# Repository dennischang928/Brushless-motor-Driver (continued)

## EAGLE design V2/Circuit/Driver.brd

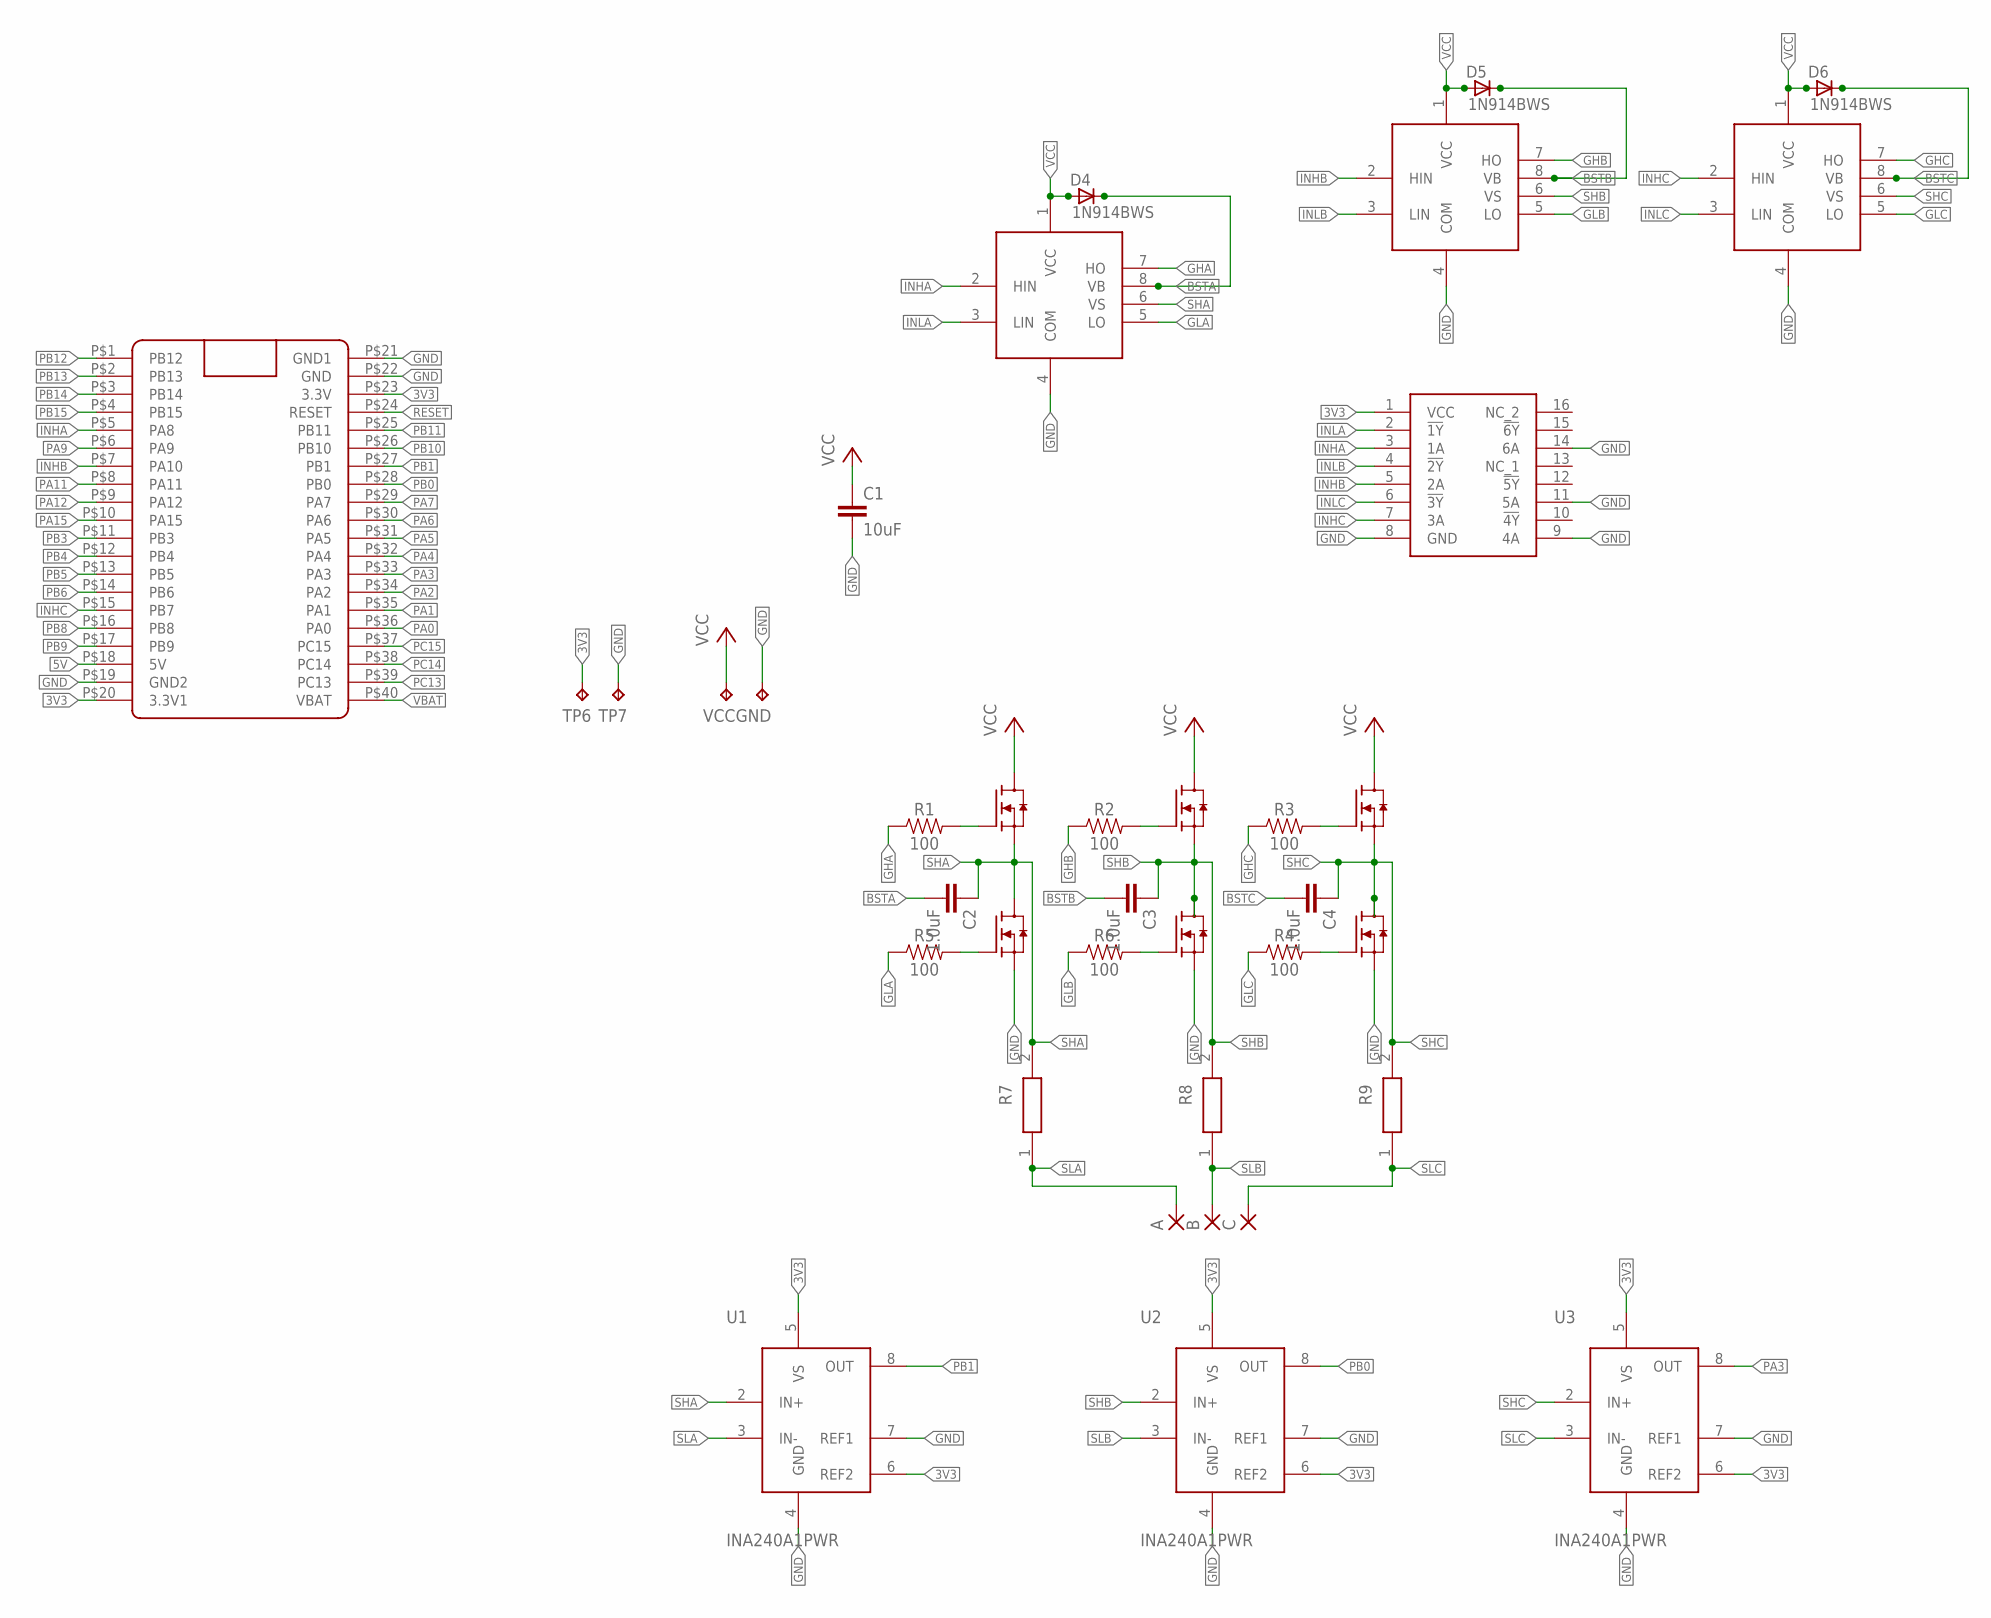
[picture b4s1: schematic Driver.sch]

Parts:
A: SMD5; SMD2,54-5,08
B: SMD5; SMD2,54-5,08
C: SMD5; SMD2,54-5,08
C1: 10uF; 0603
C2, C3, C4: 1.0uF; 0603
D4, D5, D6: 1N914BWS; SOD323F
GND: TPPAD1-13Y; P1-13Y
H-A: IRLR7843; TO252
H-B: IRLR7843; TO252
H-C: IRLR7843; TO252
IC2: CD74HC4049PWR; SOP65P640X120-16N
L-A: IRLR7843; TO252
L-B: IRLR7843; TO252
L-C: IRLR7843; TO252
R1, R2, R3, R4, R5, R6: 100; 0603
R7, R8, R9: CR2512-FX-51R1ELF; RESC6331X75N
TP6, TP7: TPPAD1-13Y; P1-13Y
U1, U2, U3: INA240A1PWR; SOP65P640X120-8N
U4, U5, U6: SOIC127P610X320-8NSOIC8; SOIC127P599X175-8N
U$1: BLUE_PILL
VCC: TPPAD1-13Y; P1-13Y

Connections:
3V3: IC2.1 (VCC), TP6.TP, U1.5 (VS), U1.6 (REF2), U2.5 (VS), U2.6 (REF2), U3.5 (VS), U3.6 (REF2), U$1.P$20 (3.3V1), U$1.P$23 (3.3V)
5V: U$1.P$18 (5V)
BSTA: C2.2, D4.C, U4.8 (VB)
BSTB: C3.2, D5.C, U5.8 (VB)
BSTC: C4.2, D6.C, U6.8 (VB)
GHA: R1.1, U4.7 (HO)
GHB: R2.1, U5.7 (HO)
GHC: R3.1, U6.7 (HO)
GLA: R5.1, U4.5 (LO)
GLB: R6.1, U5.5 (LO)
GLC: R4.1, U6.5 (LO)
GND: C1.2, GND.TP, IC2.8 (GND), IC2.9 (4A), IC2.11 (5A), IC2.14 (6A), L-A.2 (S), L-B.2 (S), L-C.2 (S), TP7.TP, U1.4 (GND), U1.7 (REF1), U2.4 (GND), U2.7 (REF1), U3.4 (GND), U3.7 (REF1), U4.4 (COM), U5.4 (COM), U6.4 (COM), U$1.P$19 (GND2), U$1.P$21 (GND1), U$1.P$22 (GND)
INHA: IC2.3 (1A), U4.2 (HIN), U$1.P$5 (PA8)
INHB: IC2.5 (2A), U5.2 (HIN), U$1.P$7 (PA10)
INHC: IC2.7 (3A), U6.2 (HIN), U$1.P$15 (PB7)
INLA: IC2.2 (!1Y), U4.3 (LIN)
INLB: IC2.4 (!2Y), U5.3 (LIN)
INLC: IC2.6 (!3Y), U6.3 (LIN)
unnamed: H-A.1 (G), R1.2
unnamed: H-B.1 (G), R2.2
unnamed: H-C.1 (G), R3.2
unnamed: L-A.1 (G), R5.2
unnamed: L-B.1 (G), R6.2
unnamed: L-C.1 (G), R4.2
PA0: U$1.P$36 (PA0)
PA1: U$1.P$35 (PA1)
PA2: U$1.P$34 (PA2)
PA3: U3.8 (OUT), U$1.P$33 (PA3)
PA4: U$1.P$32 (PA4)
PA5: U$1.P$31 (PA5)
PA6: U$1.P$30 (PA6)
PA7: U$1.P$29 (PA7)
PA9: U$1.P$6 (PA9)
PA11: U$1.P$8 (PA11)
PA12: U$1.P$9 (PA12)
PA15: U$1.P$10 (PA15)
PB0: U2.8 (OUT), U$1.P$28 (PB0)
PB1: U1.8 (OUT), U$1.P$27 (PB1)
PB3: U$1.P$11 (PB3)
PB4: U$1.P$12 (PB4)
PB5: U$1.P$13 (PB5)
PB6: U$1.P$14 (PB6)
PB8: U$1.P$16 (PB8)
PB9: U$1.P$17 (PB9)
PB10: U$1.P$26 (PB10)
PB11: U$1.P$25 (PB11)
PB12: U$1.P$1 (PB12)
PB13: U$1.P$2 (PB13)
PB14: U$1.P$3 (PB14)
PB15: U$1.P$4 (PB15)
PC13: U$1.P$39 (PC13)
PC14: U$1.P$38 (PC14)
PC15: U$1.P$37 (PC15)
RESET: U$1.P$24 (RESET)
SHA: C2.1, H-A.2 (S), L-A.3 (D), R7.2, U1.2 (IN+), U4.6 (VS)
SHB: C3.1, H-B.2 (S), L-B.3 (D), R8.2, U2.2 (IN+), U5.6 (VS)
SHC: C4.1, H-C.2 (S), L-C.3 (D), R9.2, U3.2 (IN+), U6.6 (VS)
SLA: A.1, R7.1, U1.3 (IN-)
SLB: B.1, R8.1, U2.3 (IN-)
SLC: C.1, R9.1, U3.3 (IN-)
VBAT: U$1.P$40 (VBAT)
VCC: C1.1, D4.A, D5.A, D6.A, H-A.3 (D), H-B.3 (D), H-C.3 (D), U4.1 (VCC), U5.1 (VCC), U6.1 (VCC), VCC.TP

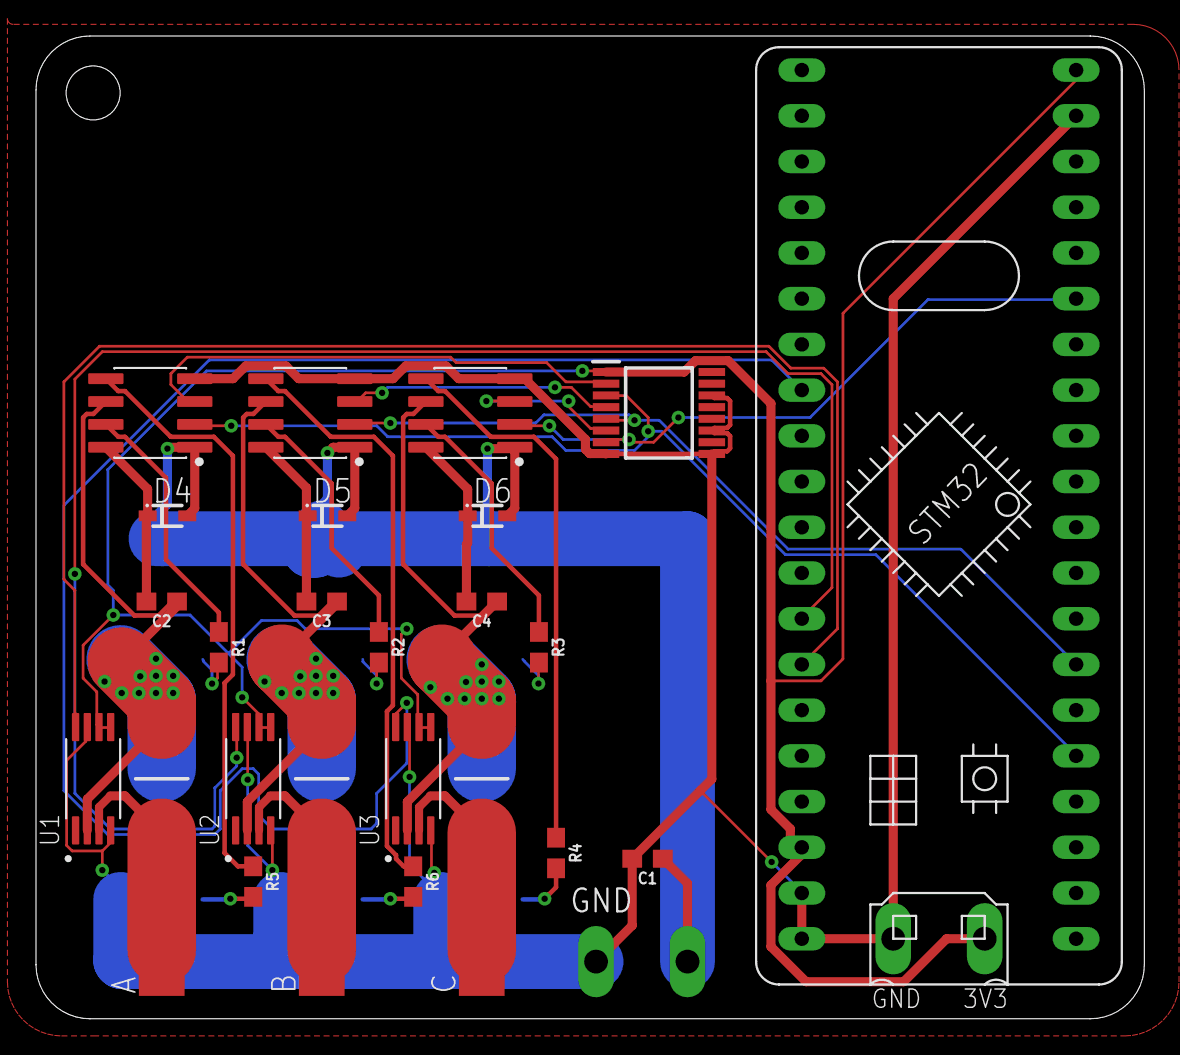
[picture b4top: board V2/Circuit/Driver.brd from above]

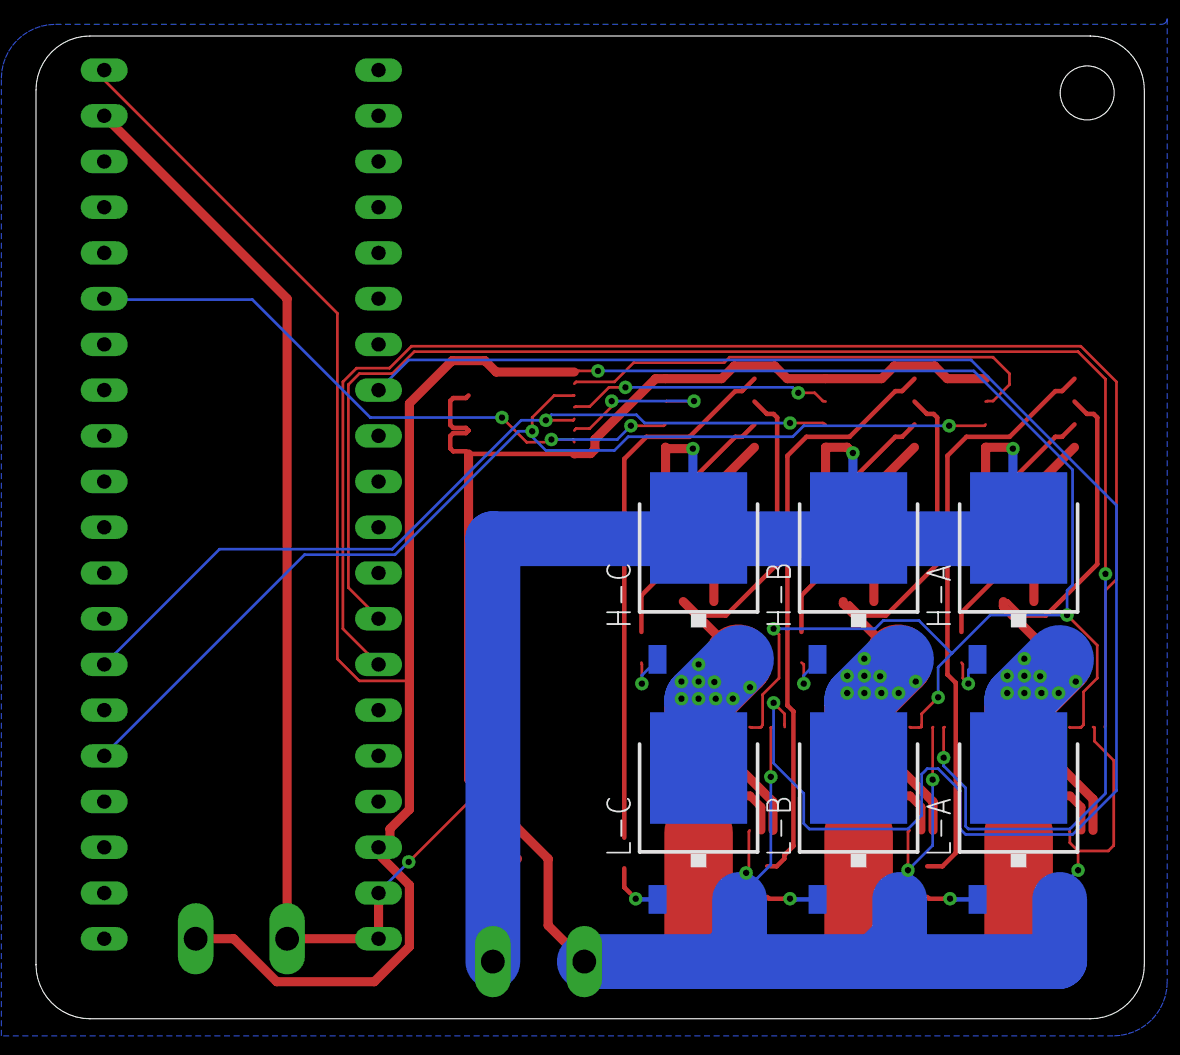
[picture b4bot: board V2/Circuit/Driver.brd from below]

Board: 2 copper layers, 61.6 x 54.6 mm, 37 parts (6 on the bottom side), 33 nets.

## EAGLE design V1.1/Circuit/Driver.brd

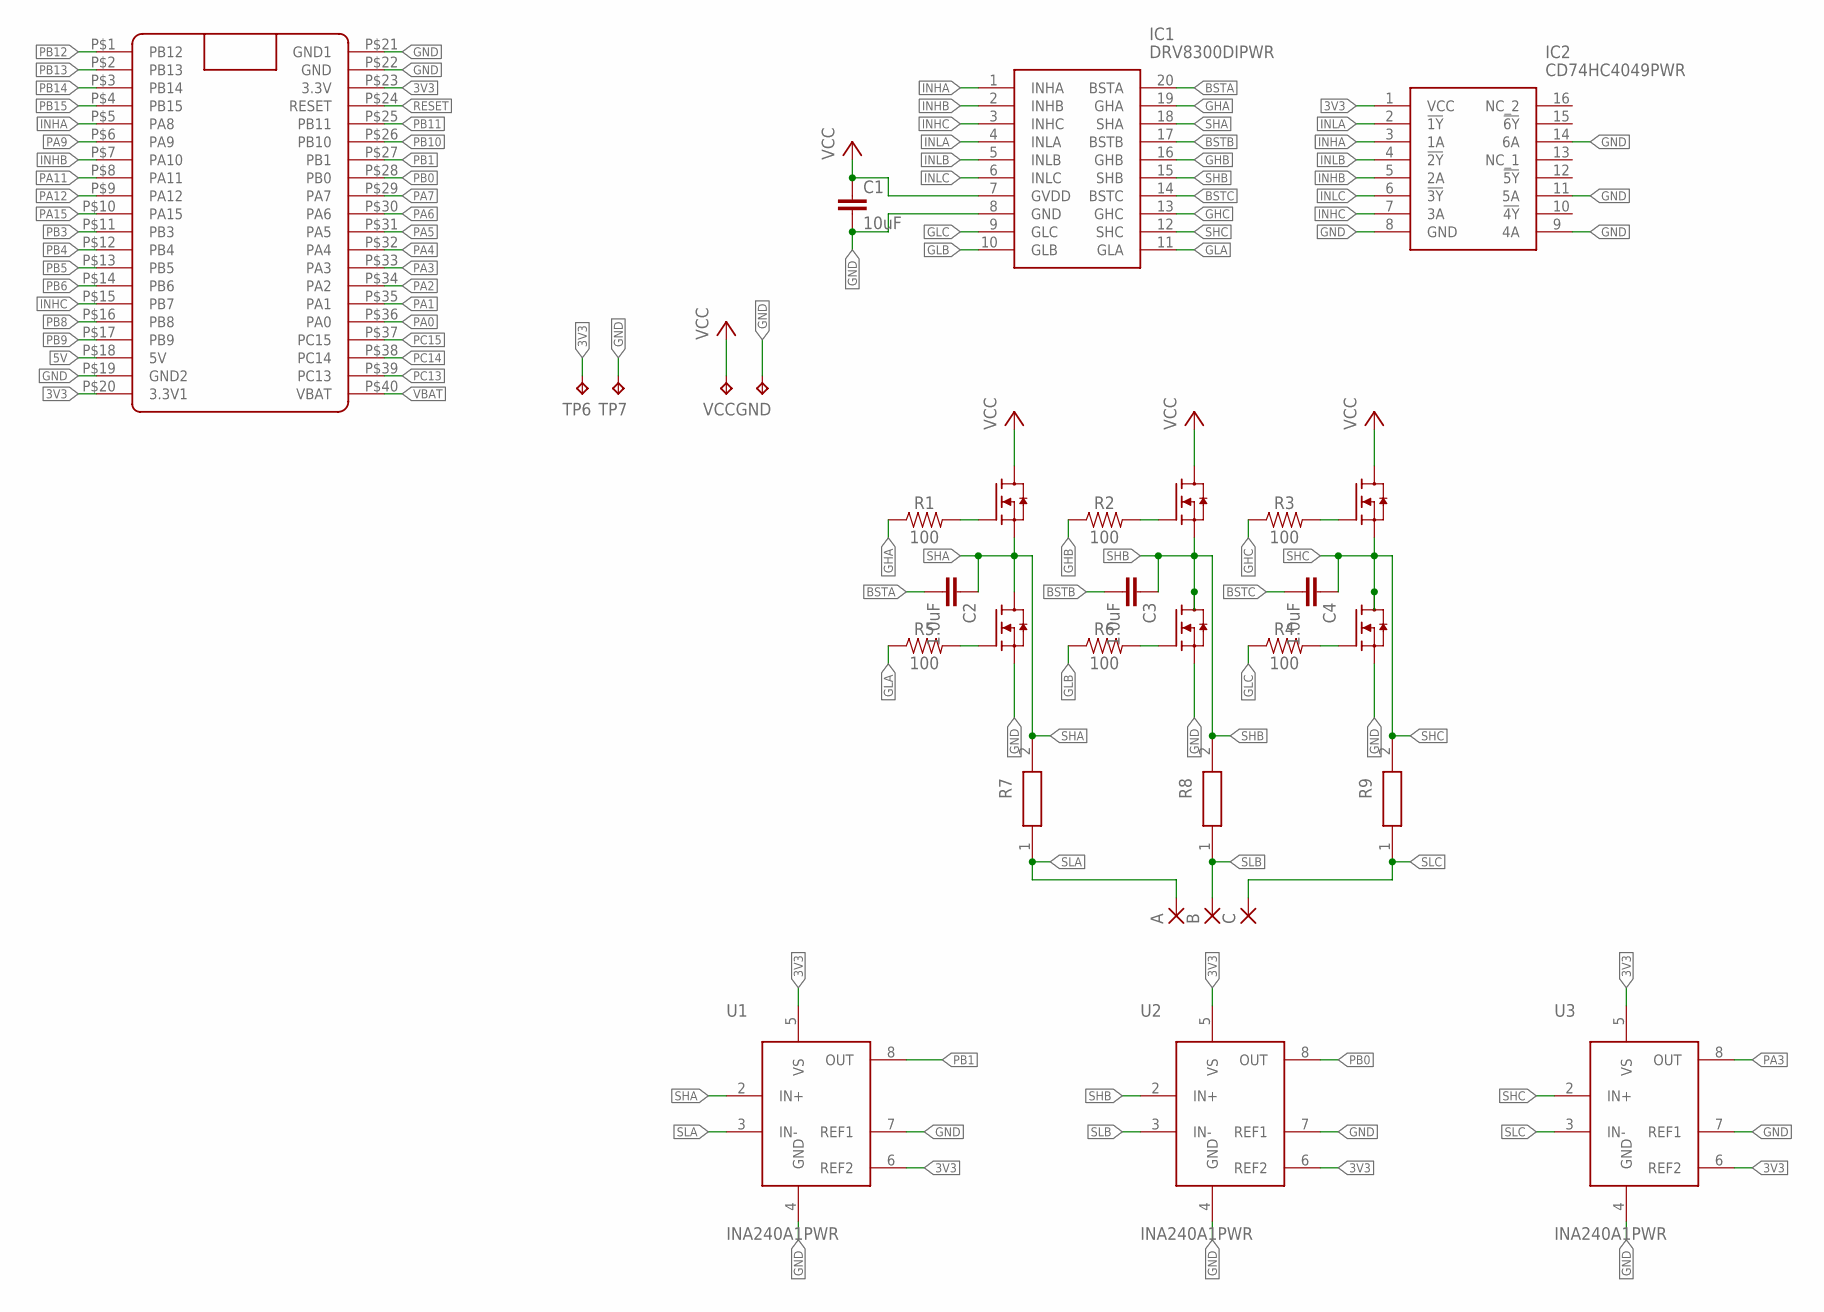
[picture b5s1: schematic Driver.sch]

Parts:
A: SMD5; SMD2,54-5,08
B: SMD5; SMD2,54-5,08
C: SMD5; SMD2,54-5,08
C1: 10uF; 0603
C2, C3, C4: 1.0uF; 0603
GND: TPPAD1-13Y; P1-13Y
IC1: DRV8300DIPWR; SOP65P640X120-20N
IC2: CD74HC4049PWR; SOP65P640X120-16N
R1, R2, R3, R4, R5, R6: 100; 0603
R7, R8, R9: CR2512-FX-51R1ELF; RESC6331X75N
TP6, TP7: TPPAD1-13Y; P1-13Y
U1, U2, U3: INA240A1PWR; SOP65P640X120-8N
U$1: BLUE_PILL
U$2, U$3, U$4, U$5, U$6, U$7: IRLR7843; TO252
VCC: TPPAD1-13Y; P1-13Y

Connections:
3V3: IC2.1 (VCC), TP6.TP, U1.5 (VS), U1.6 (REF2), U2.5 (VS), U2.6 (REF2), U3.5 (VS), U3.6 (REF2), U$1.P$20 (3.3V1), U$1.P$23 (3.3V)
5V: U$1.P$18 (5V)
BSTA: C2.2, IC1.20 (BSTA)
BSTB: C3.2, IC1.17 (BSTB)
BSTC: C4.2, IC1.14 (BSTC)
GHA: IC1.19 (GHA), R1.1
GHB: IC1.16 (GHB), R2.1
GHC: IC1.13 (GHC), R3.1
GLA: IC1.11 (GLA), R5.1
GLB: IC1.10 (GLB), R6.1
GLC: IC1.9 (GLC), R4.1
GND: C1.2, GND.TP, IC1.8 (GND), IC2.8 (GND), IC2.9 (4A), IC2.11 (5A), IC2.14 (6A), TP7.TP, U1.4 (GND), U1.7 (REF1), U2.4 (GND), U2.7 (REF1), U3.4 (GND), U3.7 (REF1), U$1.P$19 (GND2), U$1.P$21 (GND1), U$1.P$22 (GND), U$3.2 (S), U$5.2 (S), U$7.2 (S)
INHA: IC1.1 (INHA), IC2.3 (1A), U$1.P$5 (PA8)
INHB: IC1.2 (INHB), IC2.5 (2A), U$1.P$7 (PA10)
INHC: IC1.3 (INHC), IC2.7 (3A), U$1.P$15 (PB7)
INLA: IC1.4 (INLA), IC2.2 (!1Y)
INLB: IC1.5 (INLB), IC2.4 (!2Y)
INLC: IC1.6 (INLC), IC2.6 (!3Y)
unnamed: R1.2, U$2.1 (G)
unnamed: R2.2, U$4.1 (G)
unnamed: R3.2, U$6.1 (G)
unnamed: R5.2, U$3.1 (G)
unnamed: R6.2, U$5.1 (G)
unnamed: R4.2, U$7.1 (G)
PA0: U$1.P$36 (PA0)
PA1: U$1.P$35 (PA1)
PA2: U$1.P$34 (PA2)
PA3: U3.8 (OUT), U$1.P$33 (PA3)
PA4: U$1.P$32 (PA4)
PA5: U$1.P$31 (PA5)
PA6: U$1.P$30 (PA6)
PA7: U$1.P$29 (PA7)
PA9: U$1.P$6 (PA9)
PA11: U$1.P$8 (PA11)
PA12: U$1.P$9 (PA12)
PA15: U$1.P$10 (PA15)
PB0: U2.8 (OUT), U$1.P$28 (PB0)
PB1: U1.8 (OUT), U$1.P$27 (PB1)
PB3: U$1.P$11 (PB3)
PB4: U$1.P$12 (PB4)
PB5: U$1.P$13 (PB5)
PB6: U$1.P$14 (PB6)
PB8: U$1.P$16 (PB8)
PB9: U$1.P$17 (PB9)
PB10: U$1.P$26 (PB10)
PB11: U$1.P$25 (PB11)
PB12: U$1.P$1 (PB12)
PB13: U$1.P$2 (PB13)
PB14: U$1.P$3 (PB14)
PB15: U$1.P$4 (PB15)
PC13: U$1.P$39 (PC13)
PC14: U$1.P$38 (PC14)
PC15: U$1.P$37 (PC15)
RESET: U$1.P$24 (RESET)
SHA: C2.1, IC1.18 (SHA), R7.2, U1.2 (IN+), U$2.2 (S), U$3.3 (D)
SHB: C3.1, IC1.15 (SHB), R8.2, U2.2 (IN+), U$4.2 (S), U$5.3 (D)
SHC: C4.1, IC1.12 (SHC), R9.2, U3.2 (IN+), U$6.2 (S), U$7.3 (D)
SLA: A.1, R7.1, U1.3 (IN-)
SLB: B.1, R8.1, U2.3 (IN-)
SLC: C.1, R9.1, U3.3 (IN-)
VBAT: U$1.P$40 (VBAT)
VCC: C1.1, IC1.7 (GVDD), U$2.3 (D), U$4.3 (D), U$6.3 (D), VCC.TP

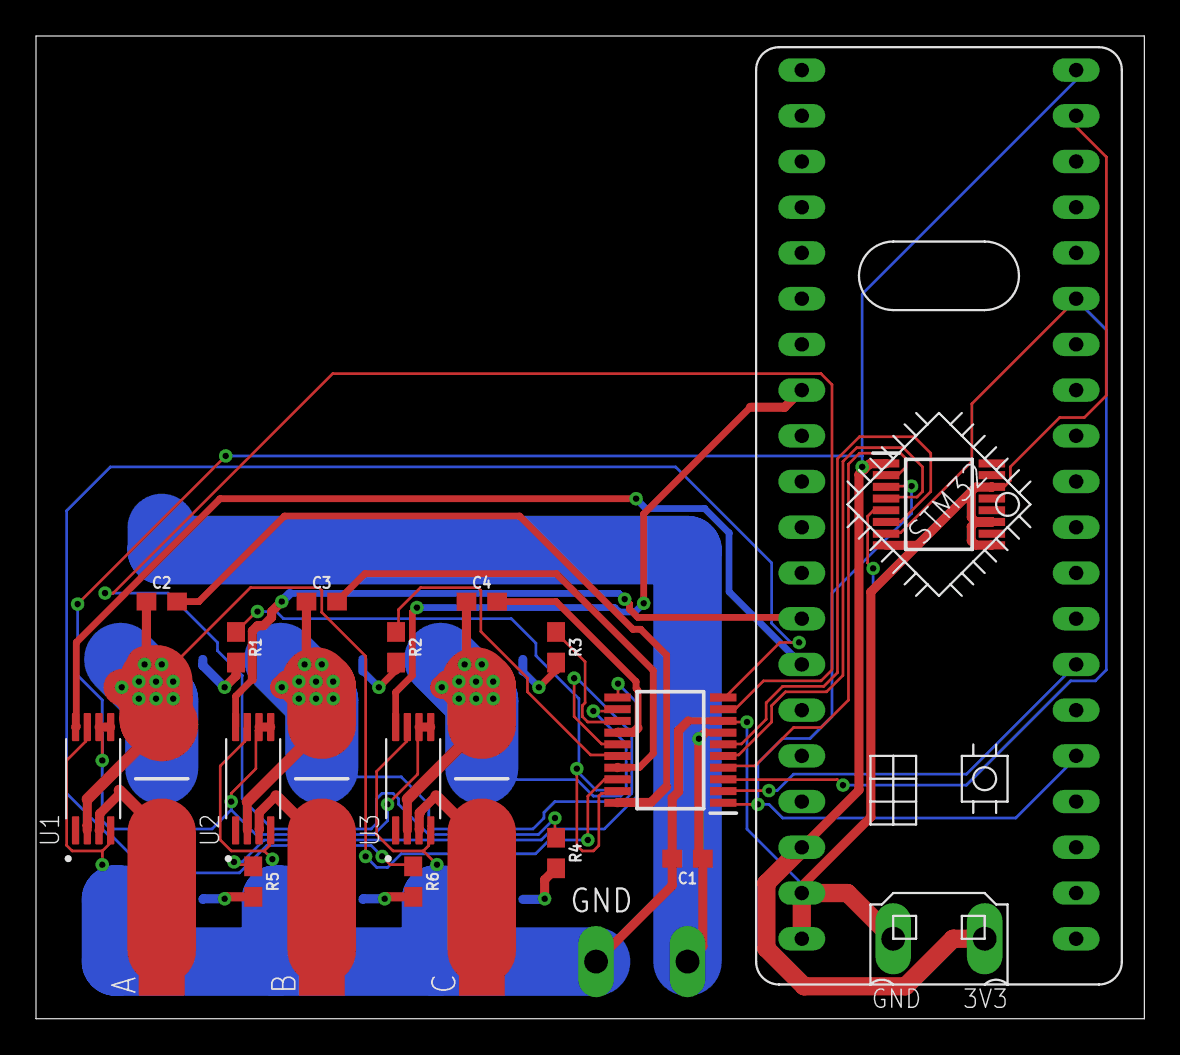
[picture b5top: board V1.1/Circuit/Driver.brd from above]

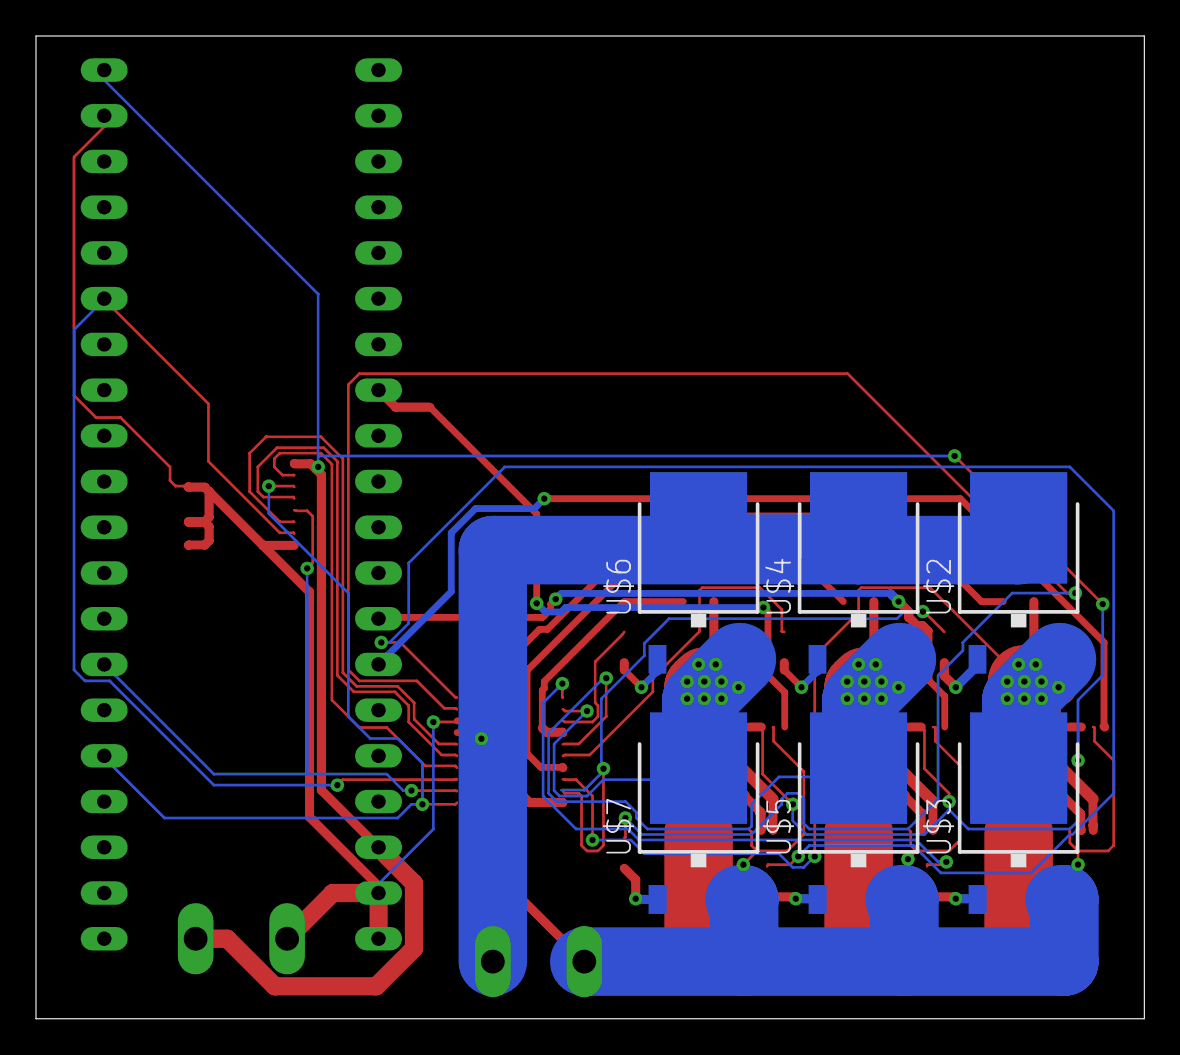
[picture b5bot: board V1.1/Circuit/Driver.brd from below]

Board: 2 copper layers, 61.6 x 54.6 mm, 32 parts (6 on the bottom side), 33 nets.

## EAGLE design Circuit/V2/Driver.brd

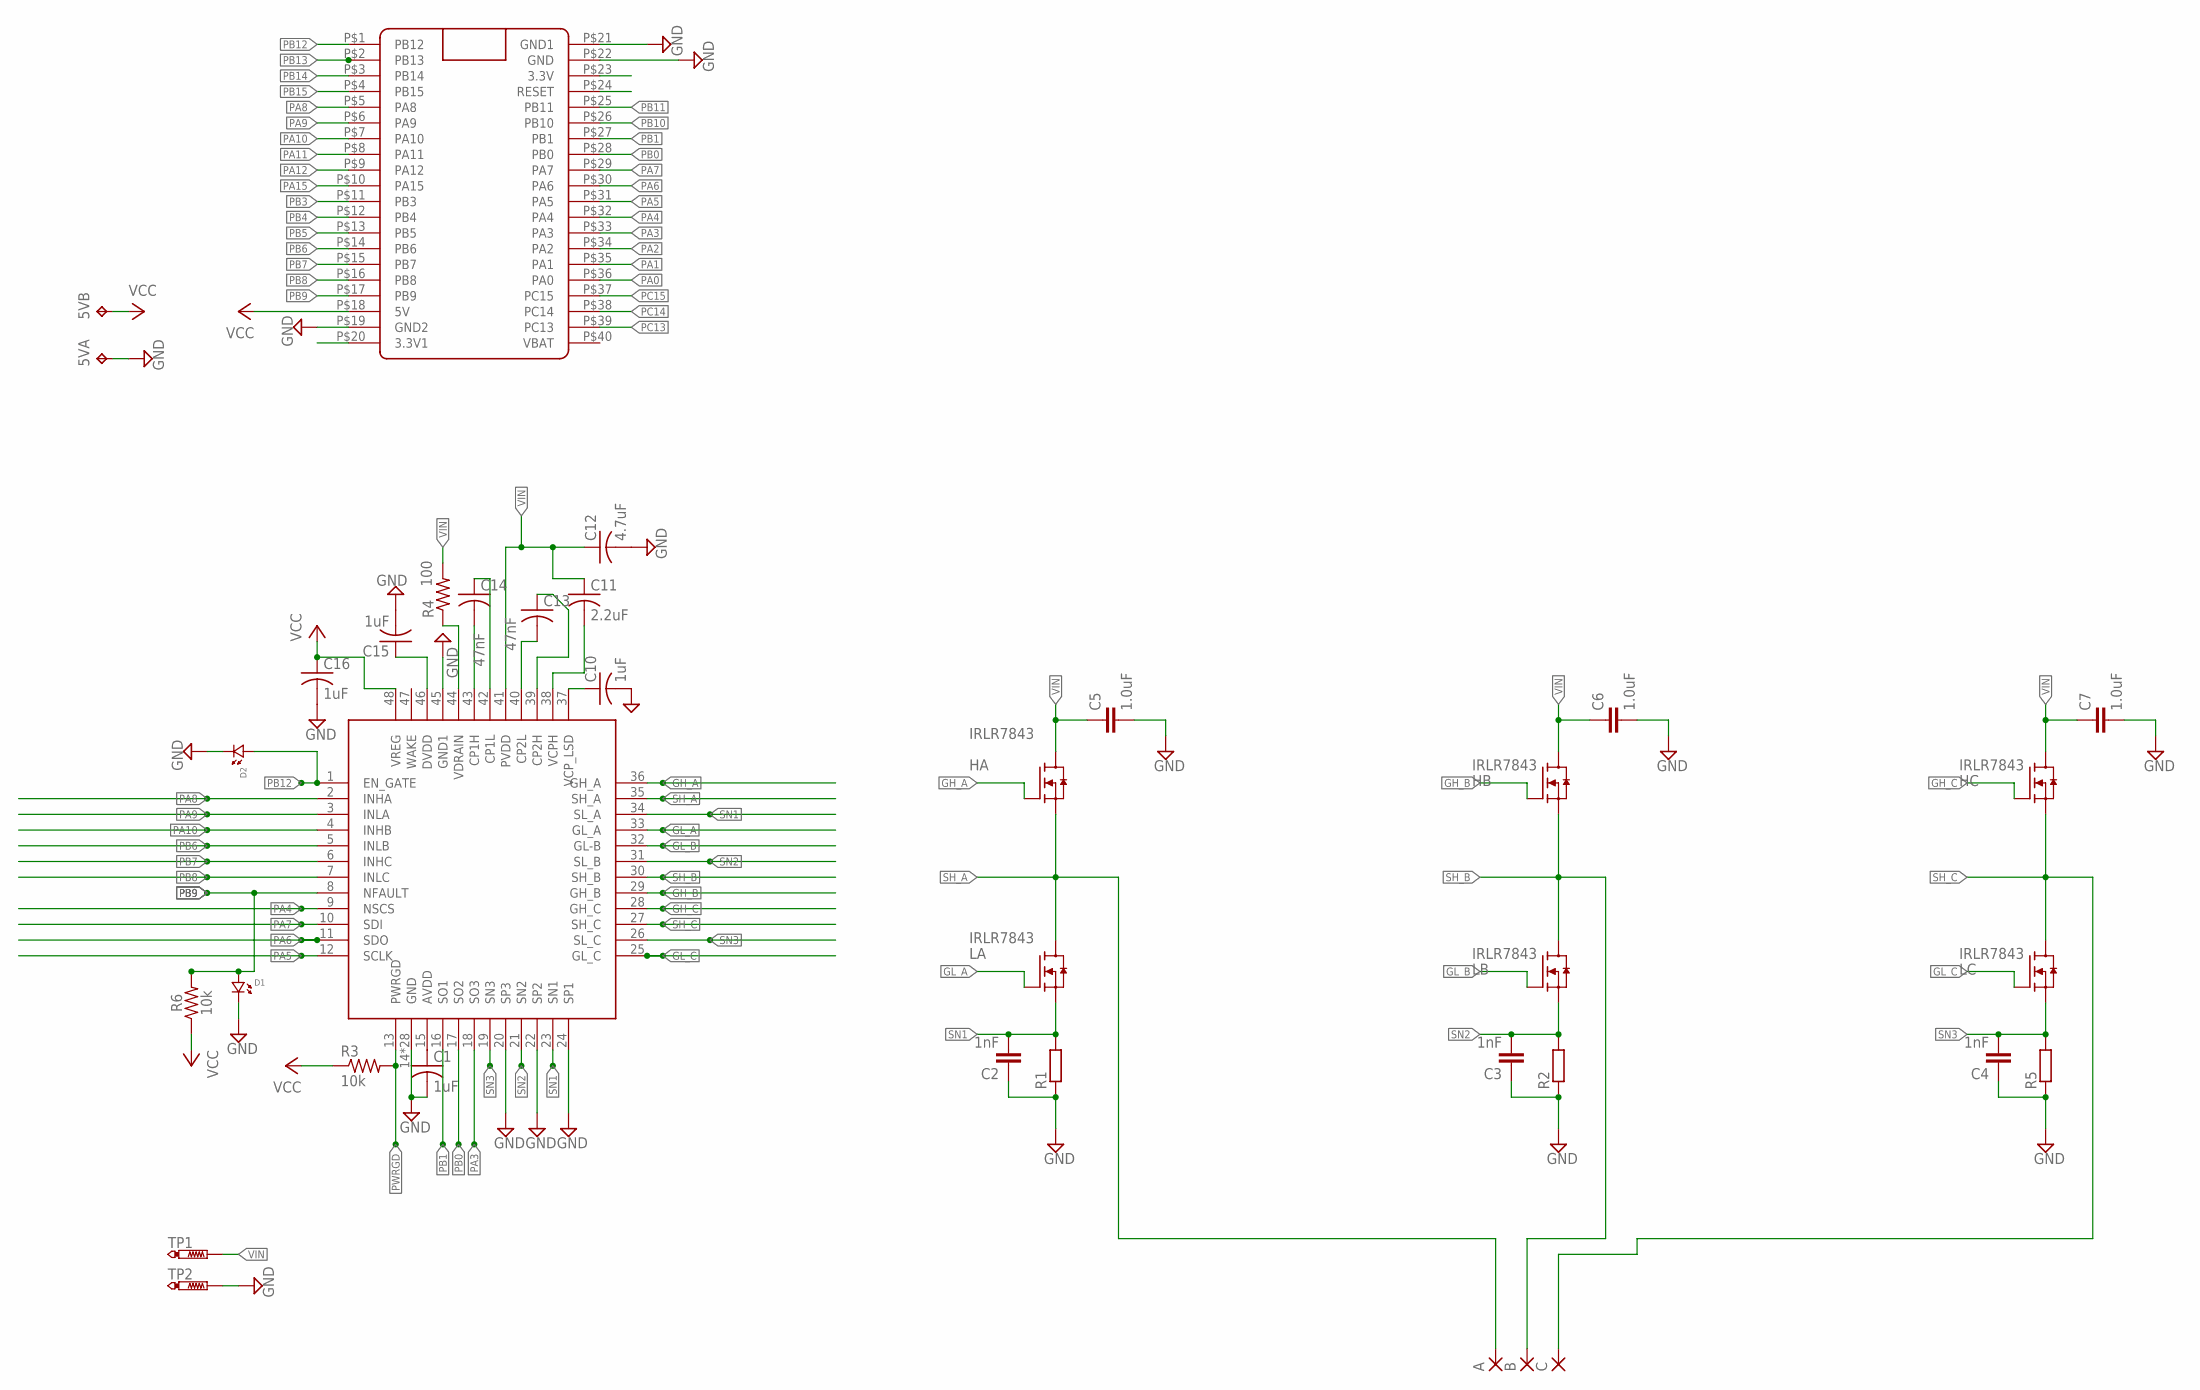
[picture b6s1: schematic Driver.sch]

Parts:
5V: TP2P2-38-17; P2-38-17
A: SMD5; SMD2,54-5,08
B: SMD5; SMD2,54-5,08
C: SMD5; SMD2,54-5,08
C1, C10, C15, C16: 1uF; C0603
C2, C3, C4: 1nF; 0603
C5, C6, C7: 1.0uF; 0603
C11: 2.2uF; C0603
C12: 4.7uF; C0603
C13, C14: 47nF; C0603
D1, D2: LED.0805; 0805.LED
HA: IRLR7843; TO252
HB: IRLR7843; TO252
HC: IRLR7843; TO252
LA: IRLR7843; TO252
LB: IRLR7843; TO252
LC: IRLR7843; TO252
R1, R2, R5: R-EU_R2512; R2512
R3: 10k; R0603
R4: 100; R0603
R6: 10k; 0603
TP1, TP2: PTR1PAD1-20Y; P1-20Y
U$1: BLUE_PILLADVANCED; BLUE_PILL_ADV
U$3: DRV8305; PFB_S-PQFP-G48

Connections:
CP1H: C14.2, U$3.43 (CP1H)
CP1L: C14.1, U$3.42 (CP1L)
CP2H: C13.1, U$3.39 (CP2H)
CP2L: C13.2, U$3.40 (CP2L)
DVDD: C15.1, U$3.46 (DVDD)
GH_A: HA.1 (G), U$3.36 (GH_A)
GH_B: HB.1 (G), U$3.29 (GH_B)
GH_C: HC.1 (G), U$3.28 (GH_C)
GL_A: LA.1 (G), U$3.33 (GL_A)
GL_B: LB.1 (G), U$3.32 (GL-B)
GL_C: LC.1 (G), U$3.25 (GL_C)
GND: 5V.TP-1, C1.2, C2.1, C3.1, C4.1, C5.2, C6.2, C7.2, C10.2, C12.2, C15.2, C16.2, D1.P$2 (2), D2.P$2 (2), R1.1, R2.1, R5.1, TP2.TP, U$1.P$19 (GND2), U$1.P$21 (GND1), U$1.P$22 (GND), U$3.14 (GND), U$3.20 (SP3), U$3.22 (SP2), U$3.24 (SP1), U$3.45 (GND1), U$3.P$1 (GND), U$3.P$2 (GND), U$3.P$3 (GND), U$3.P$4 (GND), U$3.P$5 (GND), U$3.P$6 (GND), U$3.P$7 (GND), U$3.P$8 (GND), U$3.P$9 (GND), U$3.P$10 (GND), U$3.P$11 (GND), U$3.P$12 (GND), U$3.P$13 (GND), U$3.P$14 (GND), U$3.P$15 (GND), U$3.P$16 (GND), U$3.P$17 (GND), U$3.P$18 (GND), U$3.P$19 (GND), U$3.P$20 (GND), U$3.P$21 (GND), U$3.P$22 (GND), U$3.P$23 (GND), U$3.P$24 (GND), U$3.P$25 (GND), U$3.P$26 (GND), U$3.P$27 (GND); also elsewhere on the board
unnamed: C1.1, U$3.15 (AVDD)
PA0: U$1.P$36 (PA0)
PA1: U$1.P$35 (PA1)
PA2: U$1.P$34 (PA2)
PA3: U$1.P$33 (PA3), U$3.18 (SO3)
PA4: U$1.P$32 (PA4), U$3.9 (NSCS)
PA5: U$1.P$31 (PA5), U$3.12 (SCLK)
PA6: U$1.P$30 (PA6), U$3.11 (SDO)
PA7: U$1.P$29 (PA7), U$3.10 (SDI)
PA8: U$1.P$5 (PA8), U$3.2 (INHA)
PA9: U$1.P$6 (PA9), U$3.3 (INLA)
PA10: U$1.P$7 (PA10), U$3.4 (INHB)
PA11: U$1.P$8 (PA11)
PA12: U$1.P$9 (PA12)
PA15: U$1.P$10 (PA15)
PB0: U$1.P$28 (PB0), U$3.17 (SO2)
PB1: U$1.P$27 (PB1), U$3.16 (SO1)
PB3: U$1.P$11 (PB3)
PB4: U$1.P$12 (PB4)
PB5: U$1.P$13 (PB5)
PB6: U$1.P$14 (PB6), U$3.5 (INLB)
PB7: U$1.P$15 (PB7), U$3.6 (INHC)
PB8: U$1.P$16 (PB8), U$3.7 (INLC)
PB9: D1.P$1 (1), R6.2, U$1.P$17 (PB9), U$3.8 (NFAULT); also elsewhere on the board
PB10: U$1.P$26 (PB10)
PB11: U$1.P$25 (PB11)
PB12: D2.P$1 (1), U$1.P$1 (PB12), U$3.1 (EN_GATE); also elsewhere on the board
PB13: U$1.P$2 (PB13)
PB14: U$1.P$3 (PB14)
PB15: U$1.P$4 (PB15)
PC13: U$1.P$39 (PC13)
PC14: U$1.P$38 (PC14)
PC15: U$1.P$37 (PC15)
PWRGD: R3.2, U$3.13 (PWRGD)
SH_A: A.1, HA.2 (S), LA.3 (D), U$3.35 (SH_A)
SH_B: B.1, HB.2 (S), LB.3 (D), U$3.30 (SH_B)
SH_C: C.1, HC.2 (S), LC.3 (D), U$3.27 (SH_C)
SN1: C2.2, LA.2 (S), R1.2, U$3.23 (SN1), U$3.34 (SL_A)
SN2: C3.2, LB.2 (S), R2.2, U$3.21 (SN2), U$3.31 (SL_B)
SN3: C4.2, LC.2 (S), R5.2, U$3.19 (SN3), U$3.26 (SL_C)
VCC: 5V.TP-2, C16.1, R3.1, R6.1, U$1.P$18 (5V), U$3.48 (VREG)
VCPH: C11.2, U$3.38 (VCPH)
VCP_LSD: C10.1, U$3.37 (VCP_LSD)
VDRAIN: R4.1, U$3.44 (VDRAIN)
VIN: C5.1, C6.1, C7.1, C11.1, C12.1, HA.3 (D), HB.3 (D), HC.3 (D), R4.2, TP1.TP, U$3.41 (PVDD)

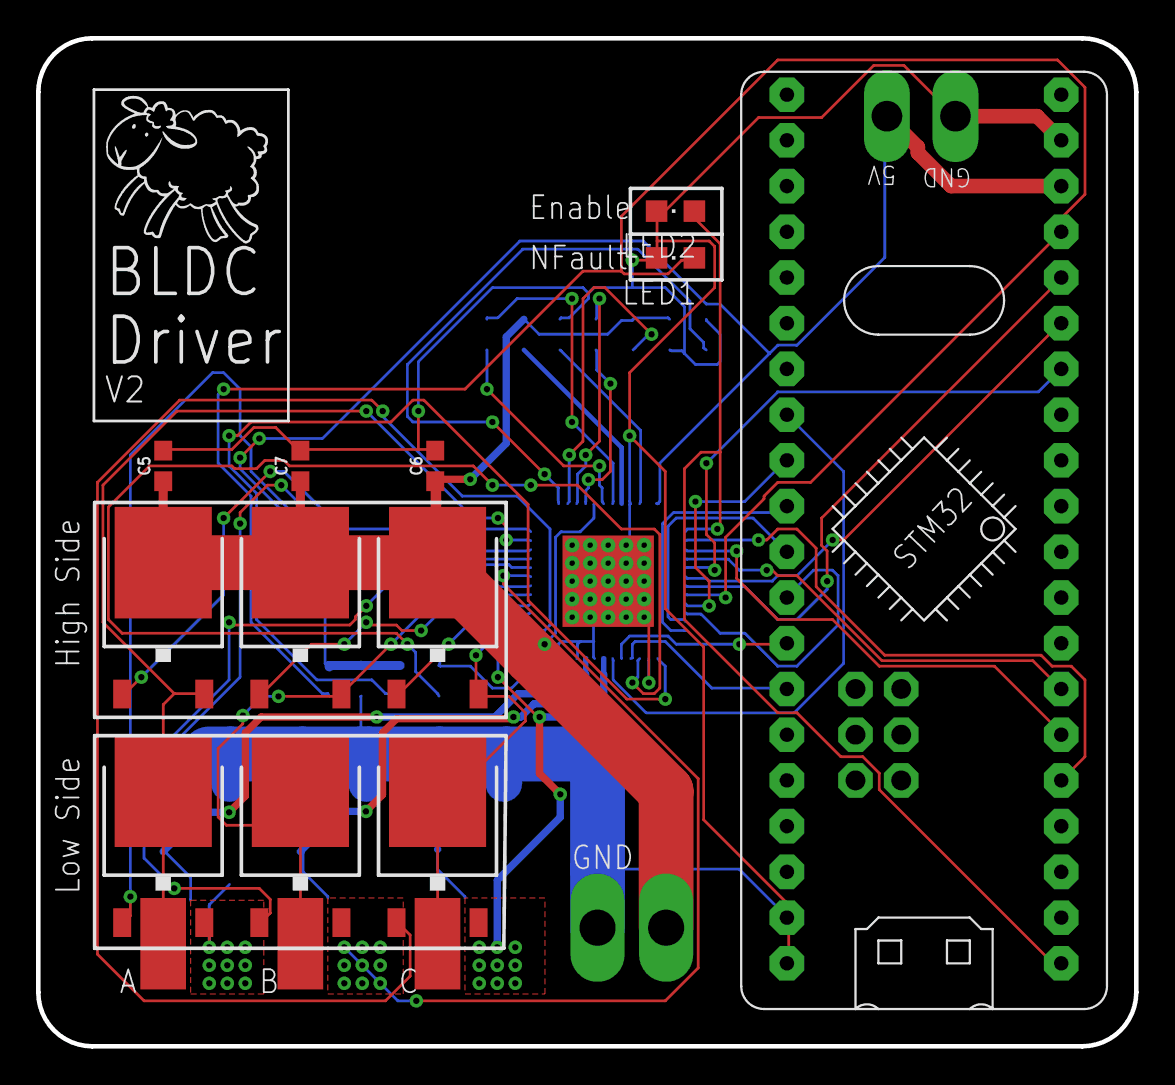
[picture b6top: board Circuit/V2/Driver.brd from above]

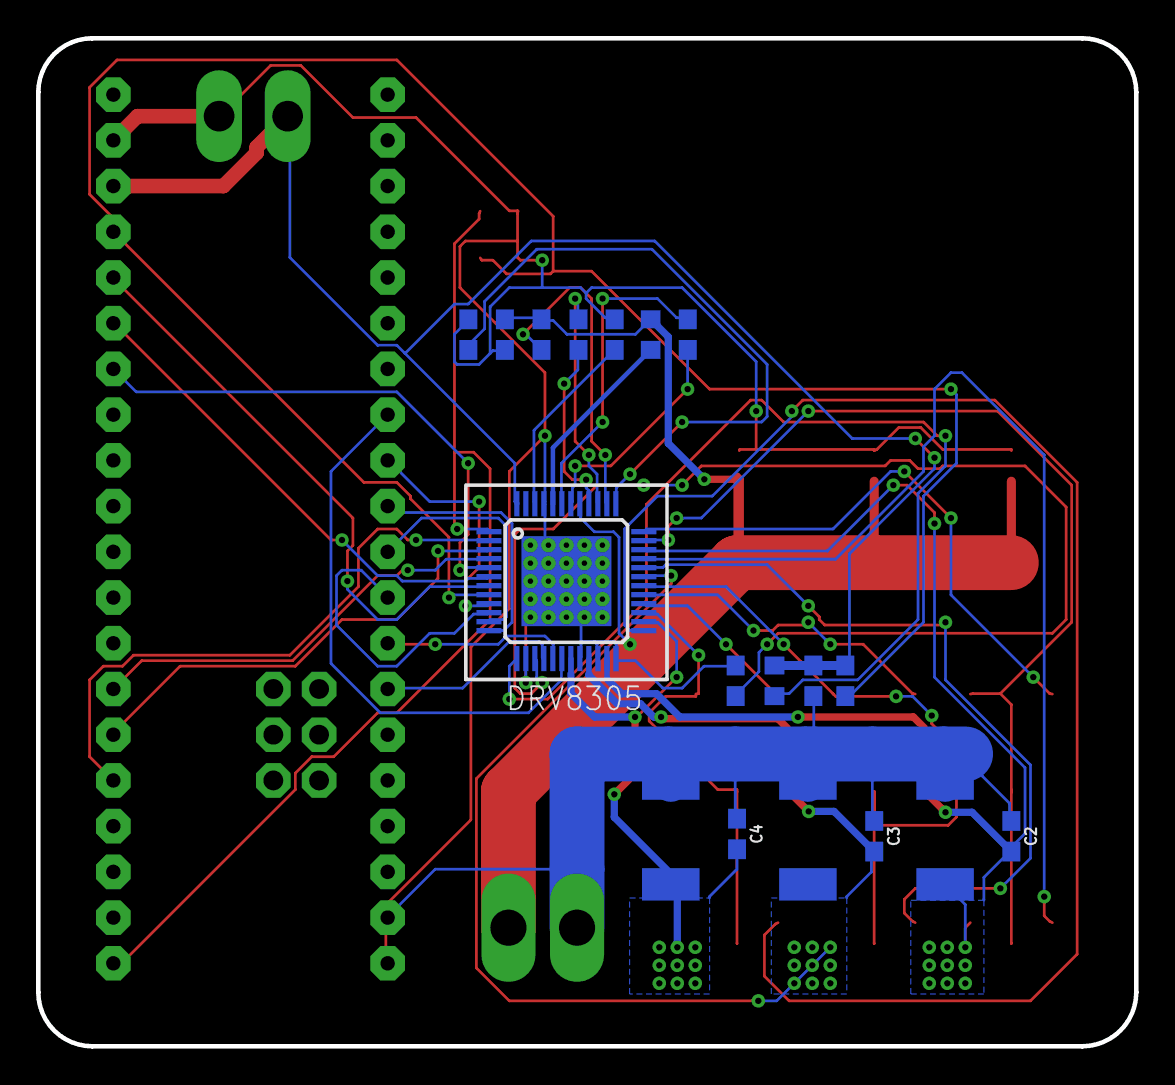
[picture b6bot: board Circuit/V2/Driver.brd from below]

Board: 2 copper layers, 61.0 x 56.0 mm, 36 parts (18 on the bottom side), 40 nets.

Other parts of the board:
LED1, LED2: CHIPLED_0805

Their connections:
GND: LED1.C, LED2.C; also elsewhere on the board
PB9: LED1.A; also elsewhere on the board
PB12: LED2.A; also elsewhere on the board
